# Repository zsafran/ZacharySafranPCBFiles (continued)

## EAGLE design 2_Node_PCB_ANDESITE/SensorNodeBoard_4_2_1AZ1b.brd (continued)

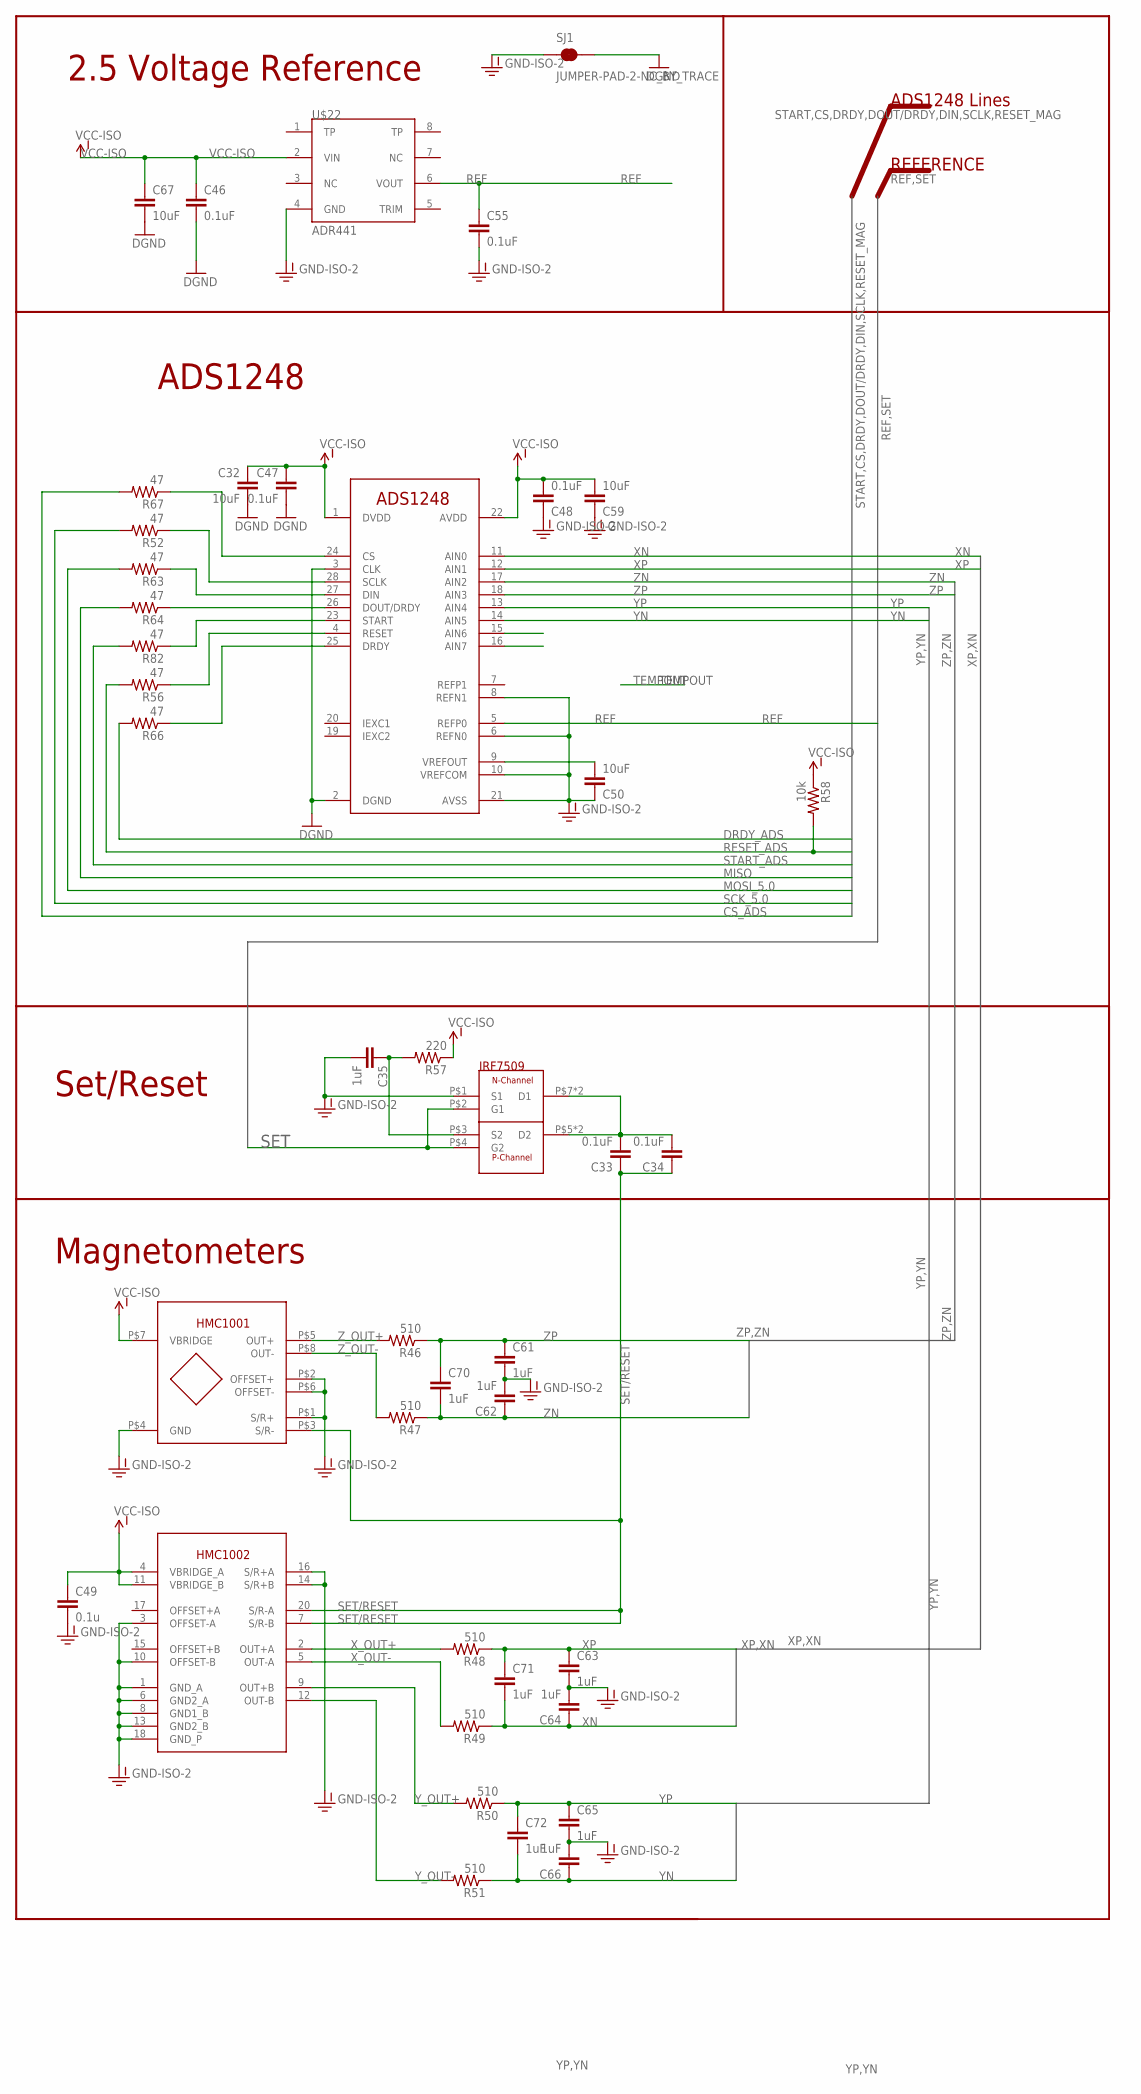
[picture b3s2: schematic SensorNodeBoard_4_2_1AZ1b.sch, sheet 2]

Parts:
C32, C50, C59, C67: 10uF; 0603-CAP
C33, C34, C46, C47, C48, C55: 0.1uF; 0603-CAP
C35, C61, C62, C63, C64, C65, C66, C70, C71, C72: 1uF; 0603-CAP
C49: 0.1u; 0603-CAP
R46, R47, R48, R49, R50, R51: 510; 0603-RES
R52, R56, R63, R64, R66, R67, R82: 47; 0603-RES
R57: 220; 0603-RES
R58: 10k; 0603-RES
SJ1: JUMPER-PAD-2-NC_BY_TRACE; PAD-JUMPER-2-NC_BY_TRACE_YES_SILK
U$7: ADS1248; TSSOP28
U$11: HMC1002; SOIC20R
U$12: HMC1001
U$17: IRF7509; MICRO8
U$22: ADR441; SOIC8

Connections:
ADS4: R56.1, U$7.4 (RESET)
ADS9: C50.2, U$7.9 (VREFOUT)
ADS15: U$7.15 (AIN6)
ADS16: U$7.16 (AIN7)
ADS23: R82.1, U$7.23 (START)
ADS24: R67.1, U$7.24 (CS)
ADS25: R66.1, U$7.25 (DRDY)
ADS26: R64.1, U$7.26 (DOUT/DRDY)
ADS27: R63.1, U$7.27 (DIN)
ADS28: R52.1, U$7.28 (SCLK)
CS_ADS: R67.2; also elsewhere on the board
DRDY_ADS: R66.2; also elsewhere on the board
GND: C32.2, C46.2, C47.2, C67.2, SJ1.2, U$7.2 (DGND), U$7.3 (CLK); also elsewhere on the board
GND-ISO-2: C35.2, C48.1, C49.2, C50.1, C55.2, C59.1, C61.2, C62.2, C63.2, C64.2, C65.2, C66.2, SJ1.1, U$7.6 (REFN0), U$7.8 (REFN1), U$7.10 (VREFCOM), U$7.21 (AVSS), U$11.1 (GND_A), U$11.3 (OFFSET-A), U$11.6 (GND2_A), U$11.8 (GND1_B), U$11.10 (OFFSET-B), U$11.13 (GND2_B), U$11.14 (S/R+B), U$11.16 (S/R+A), U$11.18 (GND_P), U$12.P$1 (S/R+), U$12.P$2 (OFFSET+), U$12.P$4 (GND), U$12.P$6 (OFFSET-), U$17.P$1 (S1), U$22.4 (GND)
MISO: R64.2; also elsewhere on the board
MOSI_5.0: R63.2; also elsewhere on the board
unnamed: C33.2, C34.2, U$17.P$5 (D2), U$17.P$6 (D2), U$17.P$7 (D1), U$17.P$8 (D1)
unnamed: C35.1, R57.2, U$17.P$3 (S2)
REF: C55.1, U$7.5 (REFP0), U$22.6 (VOUT)
RESET_ADS: R56.2, R58.2; also elsewhere on the board
SCK_5.0: R52.2; also elsewhere on the board
SET: U$17.P$2 (G1), U$17.P$4 (G2); also elsewhere on the board
SET/RESET: C33.1, C34.1, U$11.7 (S/R-B), U$11.20 (S/R-A), U$12.P$3 (S/R-)
START_ADS: R82.2; also elsewhere on the board
VCC-ISO: C32.1, C46.1, C47.1, C48.2, C49.1, C59.2, C67.1, R57.1, R58.1, U$7.1 (DVDD), U$7.22 (AVDD), U$11.4 (VBRIDGE_A), U$11.11 (VBRIDGE_B), U$12.P$7 (VBRIDGE), U$22.2 (VIN); also elsewhere on the board
XN: C64.1, C71.2, R49.1, U$7.11 (AIN0)
XP: C63.1, C71.1, R48.1, U$7.12 (AIN1)
X_OUT+: R48.2, U$11.2 (OUT+A)
X_OUT-: R49.2, U$11.5 (OUT-A)
YN: C66.1, C72.2, R51.1, U$7.14 (AIN5)
YP: C65.1, C72.1, R50.1, U$7.13 (AIN4)
Y_OUT+: R50.2, U$11.9 (OUT+B)
Y_OUT-: R51.2, U$11.12 (OUT-B)
ZN: C62.1, C70.2, R47.1, U$7.17 (AIN2)
ZP: C61.1, C70.1, R46.1, U$7.18 (AIN3)
Z_OUT+: R46.2, U$12.P$5 (OUT+)
Z_OUT-: R47.2, U$12.P$8 (OUT-)

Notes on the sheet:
ADS1248 Lines
REFERENCE
ADS1248
Magnetometers
Set/Reset
2.5 Voltage Reference

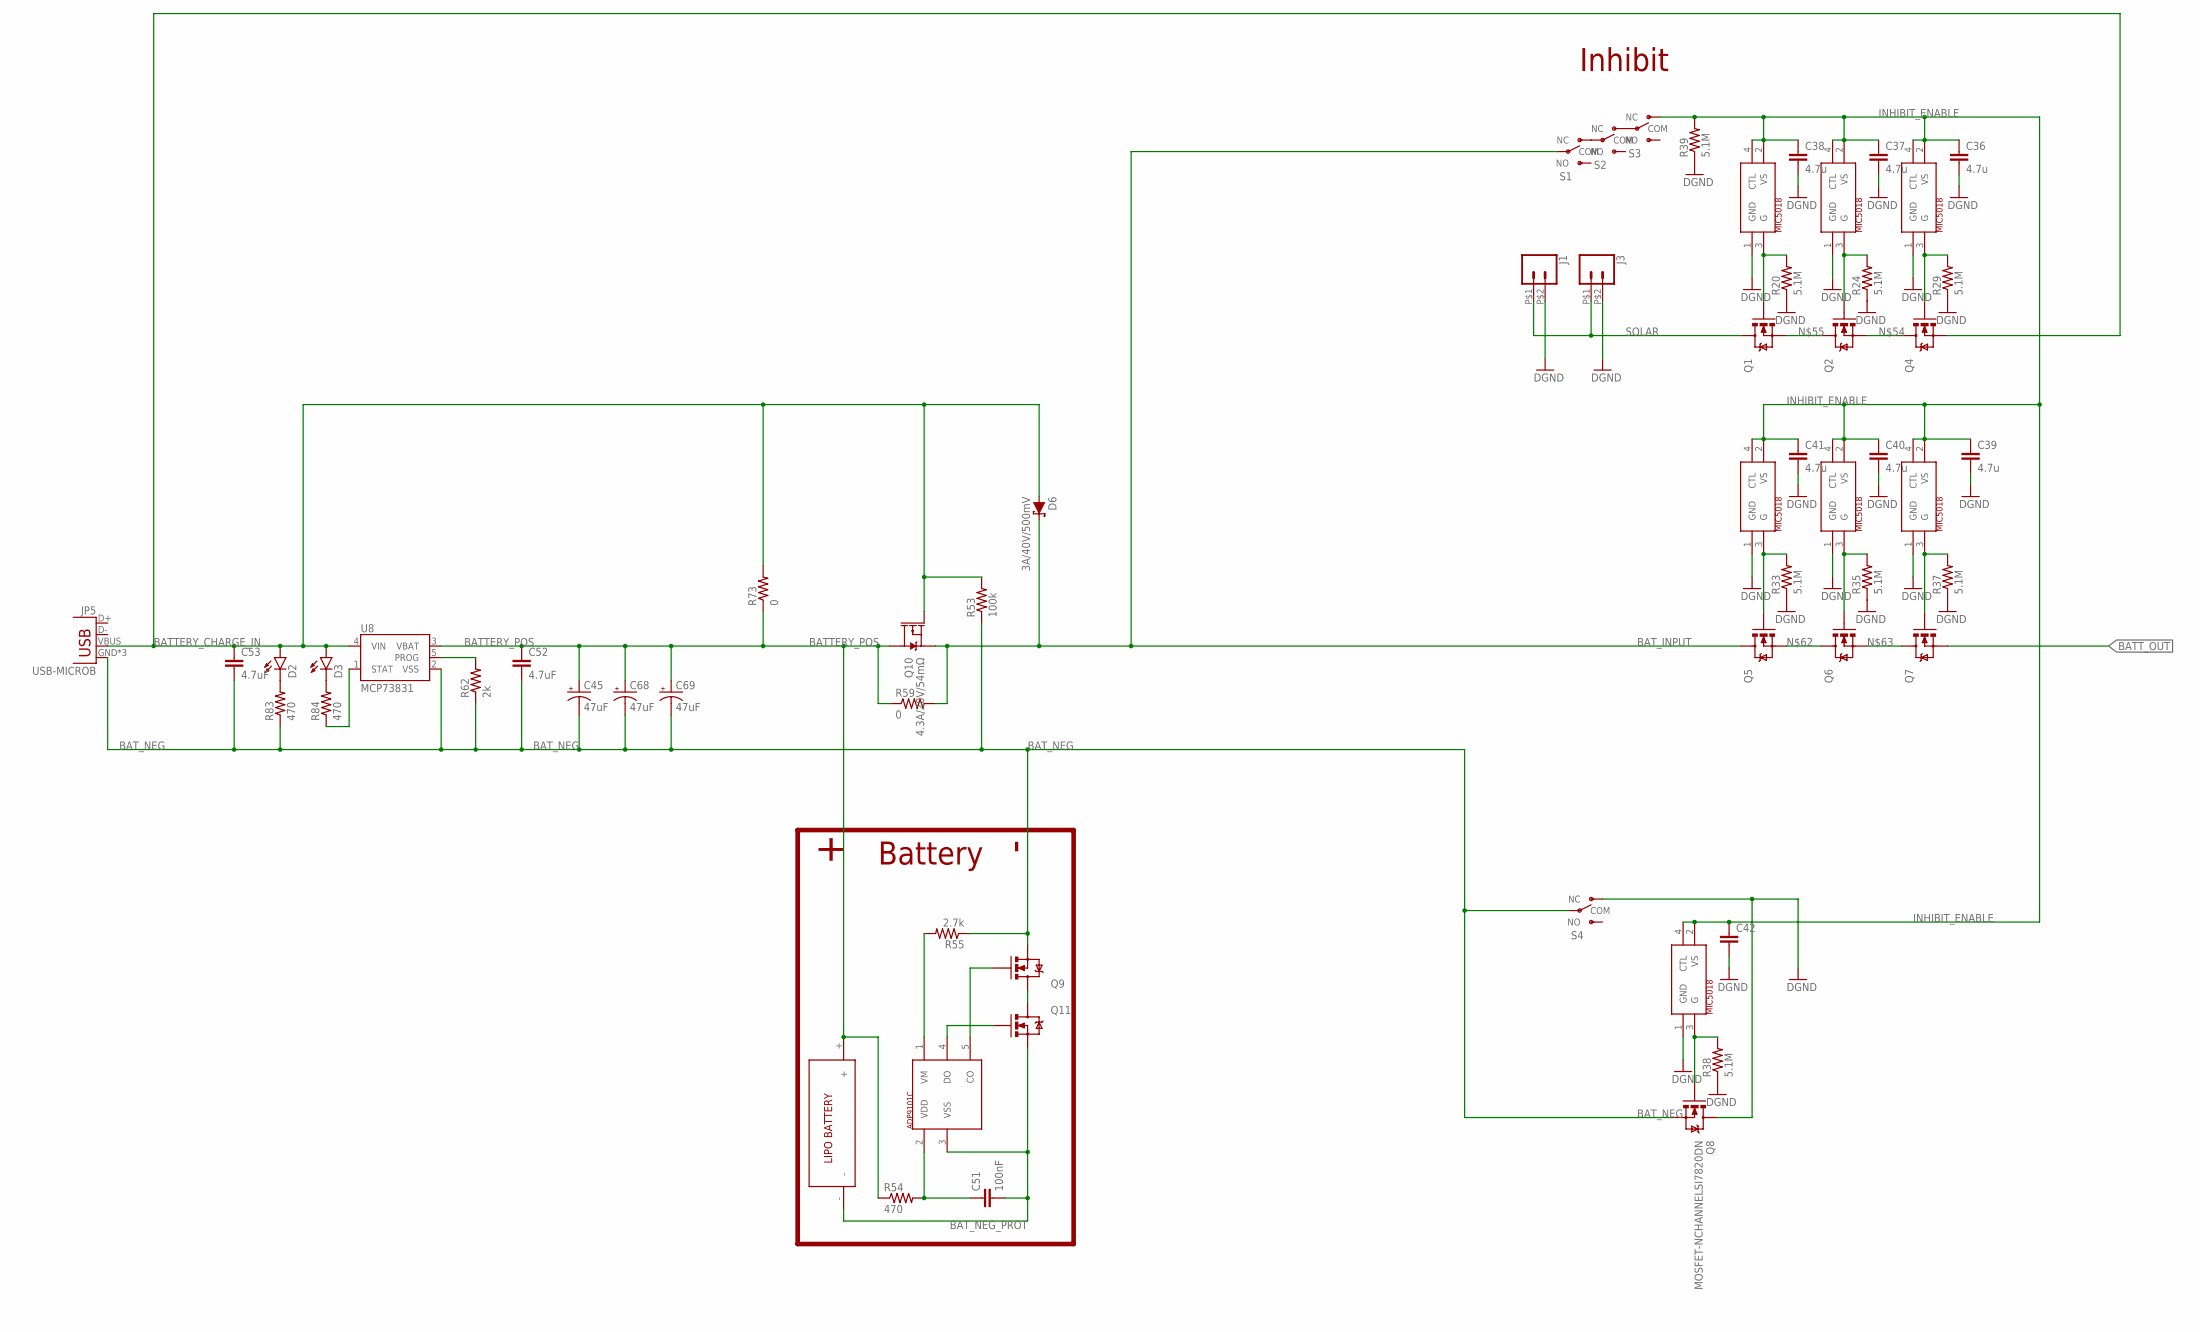
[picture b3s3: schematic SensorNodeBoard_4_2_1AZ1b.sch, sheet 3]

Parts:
C36, C37, C38, C39, C40, C41: 4.7u; 0603-CAP
C42: CAP0603-CAP; 0603-CAP
C45, C68, C69: 47uF; EIA3216
C51: 100nF; 0603-CAP
C52, C53: 4.7uF; 0603-CAP
D2, D3: LED0603; LED-0603
D6: 3A/40V/500mV; SMA-DIODE
J1, J3: CONN_02HIROSE; 1X02_1.25
JP5: USB-MICROB
Q1, Q2, Q4, Q5, Q6, Q7, Q8: MOSFET-NCHANNELSI7820DN; POWERPAK1212-8
Q9, Q11: MOSFET-NCHANNELSSM3K324R; SOT23-3@1
Q10: 4.3A/20V/54mΩ; SOT23-3
R20, R24, R29, R33, R35, R37, R38, R39: 5.1M; 0603-RES
R53: 100k; 0603-RES
R54, R83, R84: 470; 0603-RES
R55: 2.7k; 0603-RES
R59, R73: 0; R2010
R62: 2k; R0603
S1, S2, S3, S4: SWITCH-SPDT; CHERRY_SWITCH
U8: MCP73831; SOT23-5
U$8, U$13, U$14, U$15, U$16, U$19, U$20: MIC5018; SOT143
U$18: BATTERY
U$27: AP9101C; SOT25

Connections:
BATTERY_CHARGE_IN: C53.1, D2.A, D3.A, D6.A, JP5.VBUS, Q4.S1 (S), Q4.S2 (S), Q4.S3 (S), Q10.1 (G), R53.2, R73.2, U8.4 (VIN)
BATTERY_POS: C45.A (+), C52.1, C68.A (+), C69.A (+), Q10.3 (D), R54.1, R59.1, R73.1, U8.3 (VBAT), U$18.+
BATT_OUT: Q7.S1 (S), Q7.S2 (S), Q7.S3 (S); also elsewhere on the board
BAT_INPUT: D6.C, Q5.D1 (D), Q5.D2 (D), Q5.D3 (D), Q5.D4 (D), Q5.DPAD (D), Q10.2 (S), R59.2, S1.COM
BAT_NEG: C45.C (-), C52.2, C53.2, C68.C (-), C69.C (-), JP5.GND, JP5.MT1 (GND), JP5.MT2 (GND), Q8.S1 (S), Q8.S2 (S), Q8.S3 (S), Q9.2 (S), R53.1, R55.1, R62.1, R83.1, S4.COM, U8.2 (VSS)
BAT_NEG_PROT: C51.2, Q11.2 (S), U$18.-, U$27.3 (VSS)
GND: C36.2, C37.2, C38.2, C39.2, C40.2, C41.2, C42.2, J1.P$2 (2), J3.P$2 (2), Q8.D1 (D), Q8.D2 (D), Q8.D3 (D), Q8.D4 (D), Q8.DPAD (D), R20.1, R24.1, R29.1, R33.1, R35.1, R37.1, R38.1, R39.1, S4.NC, U$8.1 (GND), U$13.1 (GND), U$14.1 (GND), U$15.1 (GND), U$16.1 (GND), U$19.1 (GND), U$20.1 (GND); also elsewhere on the board
INHIBIT_ENABLE: C36.1, C37.1, C38.1, C39.1, C40.1, C41.1, C42.1, R39.2, S3.NC, U$8.2 (VS), U$8.4 (CTL), U$13.2 (VS), U$13.4 (CTL), U$14.2 (VS), U$14.4 (CTL), U$15.2 (VS), U$15.4 (CTL), U$16.2 (VS), U$16.4 (CTL), U$19.2 (VS), U$19.4 (CTL), U$20.2 (VS), U$20.4 (CTL)
unnamed: S1.NC, S2.COM
unnamed: S2.NC, S3.COM
unnamed: Q1.G, R20.2, U$8.3 (G)
unnamed: Q2.G, R24.2, U$13.3 (G)
unnamed: Q4.G, R29.2, U$14.3 (G)
unnamed: Q2.S1 (S), Q2.S2 (S), Q2.S3 (S), Q4.D1 (D), Q4.D2 (D), Q4.D3 (D), Q4.D4 (D), Q4.DPAD (D)
unnamed: Q1.S1 (S), Q1.S2 (S), Q1.S3 (S), Q2.D1 (D), Q2.D2 (D), Q2.D3 (D), Q2.D4 (D), Q2.DPAD (D)
unnamed: D2.C, R83.2
unnamed: Q11.1 (G), U$27.4 (DO)
unnamed: Q5.G, R33.2, U$15.3 (G)
unnamed: Q6.G, R35.2, U$16.3 (G)
unnamed: Q7.G, R37.2, U$19.3 (G)
unnamed: Q5.S1 (S), Q5.S2 (S), Q5.S3 (S), Q6.D1 (D), Q6.D2 (D), Q6.D3 (D), Q6.D4 (D), Q6.DPAD (D)
unnamed: Q6.S1 (S), Q6.S2 (S), Q6.S3 (S), Q7.D1 (D), Q7.D2 (D), Q7.D3 (D), Q7.D4 (D), Q7.DPAD (D)
unnamed: Q8.G, R38.2, U$20.3 (G)
unnamed: Q9.1 (G), U$27.5 (CO)
unnamed: Q9.3 (D), Q11.3 (D)
unnamed: R62.2, U8.5 (PROG)
unnamed: R55.2, U$27.1 (VM)
unnamed: C51.1, R54.2, U$27.2 (VDD)
unnamed: D3.C, R84.2
unnamed: R84.1, U8.1 (STAT)
SOLAR: J1.P$1 (1), J3.P$1 (1), Q1.D1 (D), Q1.D2 (D), Q1.D3 (D), Q1.D4 (D), Q1.DPAD (D)

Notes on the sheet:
Battery
Inhibit

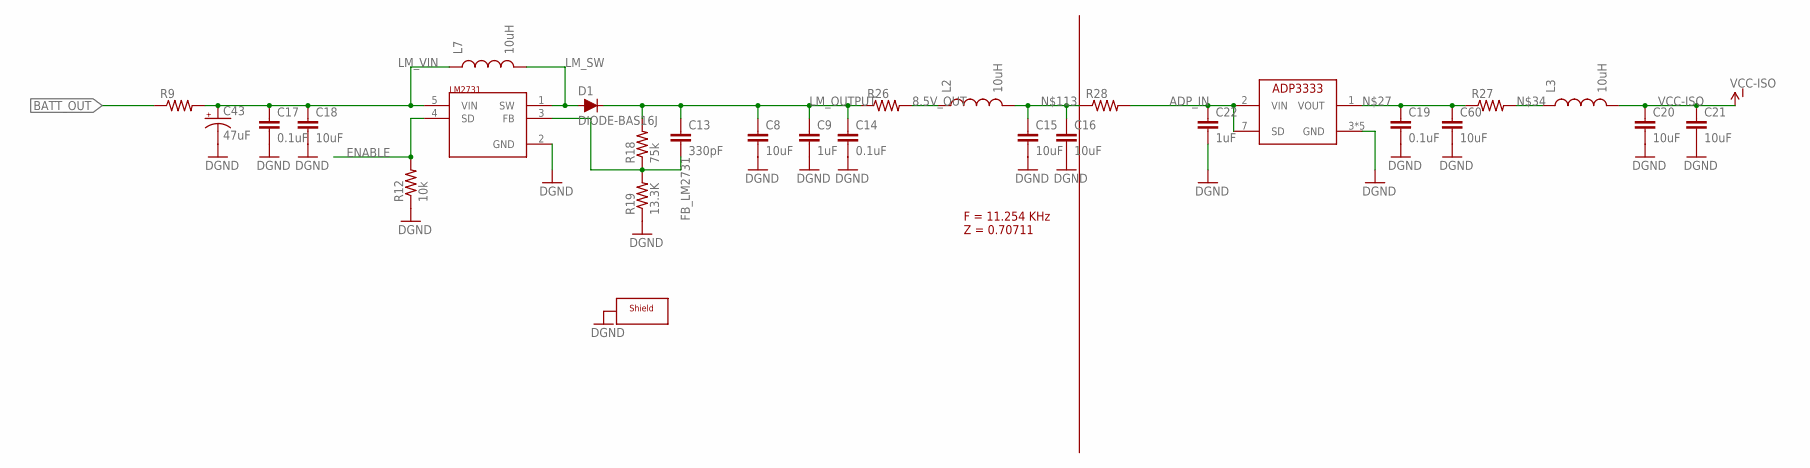
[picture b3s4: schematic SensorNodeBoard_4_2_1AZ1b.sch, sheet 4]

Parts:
C8, C15, C16, C18, C20, C21, C60: 10uF; 0603-CAP
C9, C22: 1uF; 0603-CAP
C13: 330pF; 0603-CAP
C14, C17, C19: 0.1uF; 0603-CAP
C43: 47uF; EIA3216
D1: DIODE-BAS16J; SOD-323
L2, L3, L7: 10uH; 1210
R9, R26, R27, R28: RESISTOR1206; 1206
R12: 10k; 0603-RES
R18: 75k; 0603-RES
R19: 13.3K; 0603-RES
U$4: LM2731; SOT23-5
U$6: ADP3333; MSOP-8
U$37: SHEILD2; SHIELD_BMI-S-209-C

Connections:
8.5V_OUT: L2.1, R26.2
ADP_IN: C22.1, R28.2, U$6.2 (VIN), U$6.7 (SD)
BATT_OUT: R9.1; also elsewhere on the board
ENABLE: R12.2, U$4.4 (SD); also elsewhere on the board
FB_LM2731: C13.2, R18.1, R19.2, U$4.3 (FB)
GND: C8.2, C9.2, C14.2, C15.2, C16.2, C17.2, C18.2, C19.2, C20.2, C21.2, C22.2, C43.C (-), C60.2, R12.1, R19.1, U$4.2 (GND), U$6.3 (GND), U$6.4 (GND), U$6.5 (GND), U$6.6 (GND), U$6.8 (GND), U$37.P$1, U$37.P$2, U$37.P$3, U$37.P$4, U$37.P$5, U$37.P$6, U$37.P$7, U$37.P$8, U$37.P$9, U$37.P$10, U$37.P$11, U$37.P$12, U$37.P$13, U$37.P$14, U$37.P$15, U$37.P$16; also elsewhere on the board
LM_OUTPUT: C8.1, C9.1, C13.1, C14.1, D1.C, R18.2, R26.1
LM_SW: D1.A, L7.2, U$4.1 (SW)
LM_VIN: C17.1, C18.1, C43.A (+), L7.1, R9.2, U$4.5 (VIN)
unnamed: C19.1, C60.1, R27.1, U$6.1 (VOUT)
unnamed 79: L3.1, R27.2; also elsewhere on the board
unnamed: C15.1, C16.1, L2.2, R28.1
VCC-ISO: C20.1, C21.1, L3.2; also elsewhere on the board

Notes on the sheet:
F = 11.254 KHz Z = 0.70711

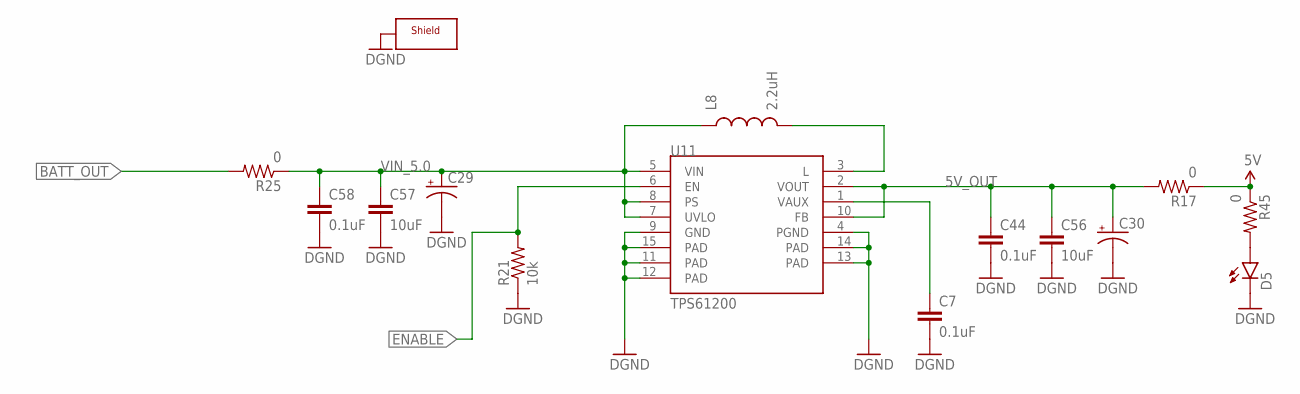
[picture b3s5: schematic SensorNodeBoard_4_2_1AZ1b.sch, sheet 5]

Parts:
C7, C44, C58: 0.1uF; 0603-CAP
C29, C30: CAP_POL1206; EIA3216
C56, C57: 10uF; 0603-CAP
D5: LED0603; LED-0603
L8: 2.2uH; 1210
R17, R25: 0; 1206
R21: 10k; 0603-RES
R45: 0; 0603-RES
U11: TPS61200; QFN-10_PAD
U$39: SHEILD; SHIELD_BMI-S-201-C

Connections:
5V: R17.1, R45.1; also elsewhere on the board
5V_OUT: C30.A (+), C44.1, C56.1, R17.2, U11.2 (VOUT), U11.10 (FB)
BATT_OUT: R25.2; also elsewhere on the board
ENABLE: R21.2, U11.6 (EN); also elsewhere on the board
GND: C7.2, C29.C (-), C30.C (-), C44.2, C56.2, C57.2, C58.2, D5.C, R21.1, U11.4 (PGND), U11.9 (GND), U11.11 (PAD), U11.12 (PAD), U11.13 (PAD), U11.14 (PAD), U11.15 (PAD), U$39.P$1, U$39.P$2, U$39.P$3, U$39.P$4, U$39.P$5, U$39.P$6, U$39.P$7, U$39.P$8, U$39.P$9, U$39.P$10, U$39.P$11, U$39.P$12; also elsewhere on the board
unnamed: L8.2, U11.3 (L)
unnamed: C7.1, U11.1 (VAUX)
unnamed: D5.A, R45.2
VIN_5.0: C29.A (+), C57.1, C58.1, L8.1, R25.1, U11.5 (VIN), U11.7 (UVLO), U11.8 (PS)

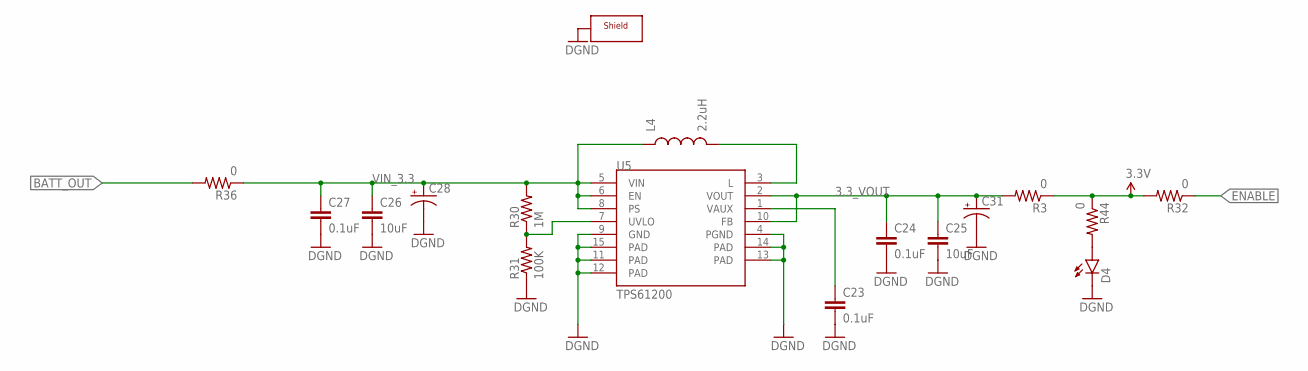
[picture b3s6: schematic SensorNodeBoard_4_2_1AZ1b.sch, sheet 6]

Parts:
C23, C24, C27: 0.1uF; 0603-CAP
C25, C26: 10uF; 0603-CAP
C28, C31: CAP_POL1206; EIA3216
D4: LED0603; LED-0603
L4: 2.2uH; 1210
R3, R36: 0; 1206
R30: 1M; 0603-RES
R31: 100K; 0603-RES
R32, R44: 0; 0603-RES
U5: TPS61200; QFN-10_PAD
U$41: SHEILD; SHIELD_BMI-S-201-C

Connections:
3.3V: R3.1, R32.2, R44.1; also elsewhere on the board
3.3_UVLO: R30.1, R31.2, U5.7 (UVLO)
3.3_VOUT: C24.1, C25.1, C31.A (+), R3.2, U5.2 (VOUT), U5.10 (FB)
BATT_OUT: R36.2; also elsewhere on the board
ENABLE: R32.1; also elsewhere on the board
GND: C23.2, C24.2, C25.2, C26.2, C27.2, C28.C (-), C31.C (-), D4.C, R31.1, U5.4 (PGND), U5.9 (GND), U5.11 (PAD), U5.12 (PAD), U5.13 (PAD), U5.14 (PAD), U5.15 (PAD), U$41.P$1, U$41.P$2, U$41.P$3, U$41.P$4, U$41.P$5, U$41.P$6, U$41.P$7, U$41.P$8, U$41.P$9, U$41.P$10, U$41.P$11, U$41.P$12; also elsewhere on the board
unnamed: L4.2, U5.3 (L)
unnamed: C23.1, U5.1 (VAUX)
unnamed: D4.A, R44.2
VIN_3.3: C26.1, C27.1, C28.A (+), L4.1, R30.2, R36.1, U5.5 (VIN), U5.6 (EN), U5.8 (PS)

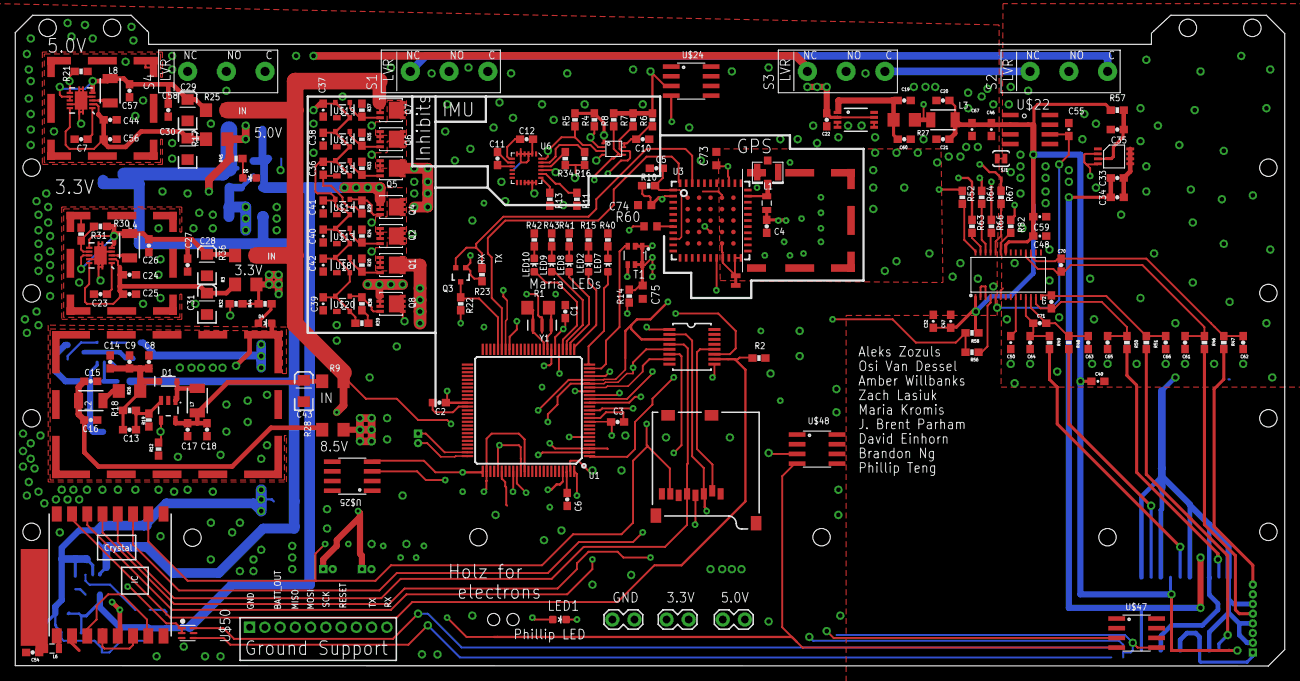
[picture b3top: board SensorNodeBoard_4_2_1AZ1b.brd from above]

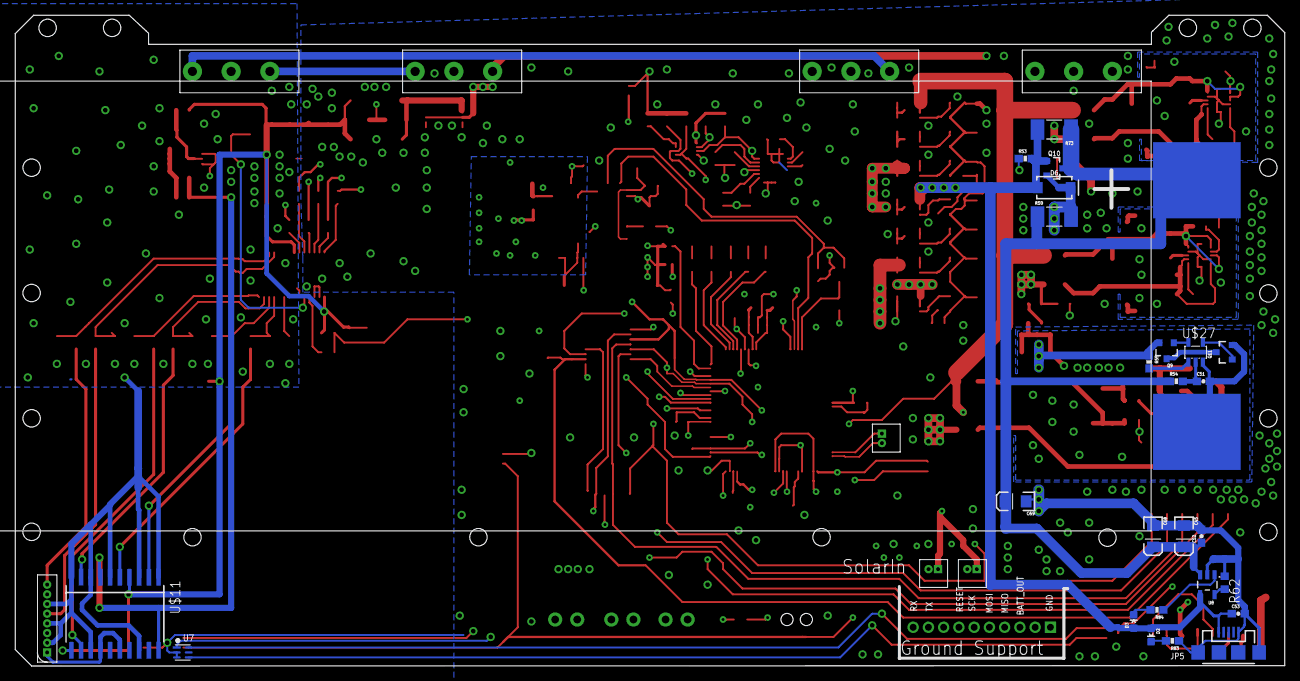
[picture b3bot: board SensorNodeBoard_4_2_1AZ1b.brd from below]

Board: 4 copper layers, 166.5 x 85.3 mm, 228 parts (30 on the bottom side), 143 nets.

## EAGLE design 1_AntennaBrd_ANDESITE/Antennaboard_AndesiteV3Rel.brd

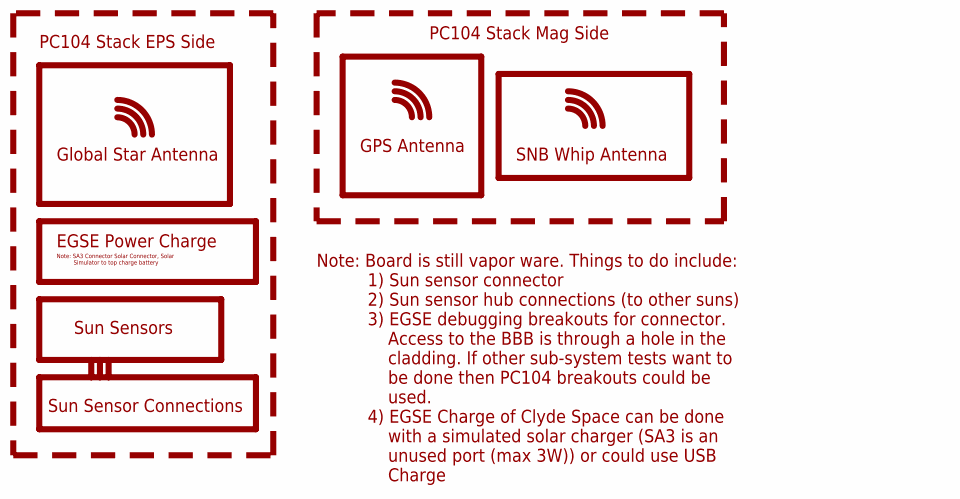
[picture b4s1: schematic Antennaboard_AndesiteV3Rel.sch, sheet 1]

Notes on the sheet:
GPS Antenna
Global Star Antenna
SNB Whip Antenna
PC104 Stack EPS Side
PC104 Stack Mag Side
Sun Sensors
EGSE Power Charge
Note: SA3 Connector Solar Connector, Solar Simulator to top charge battery
Sun Sensor Connections
Note: Board is still vapor ware. Things to do include: 1) Sun sensor connector 2) Sun sensor hub connections (to other suns) 3) EGSE debugging breakouts for connector. Access to the BBB is through a hole in the cladding. If other sub-system tests want to be done then PC104 breakouts could be used. 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

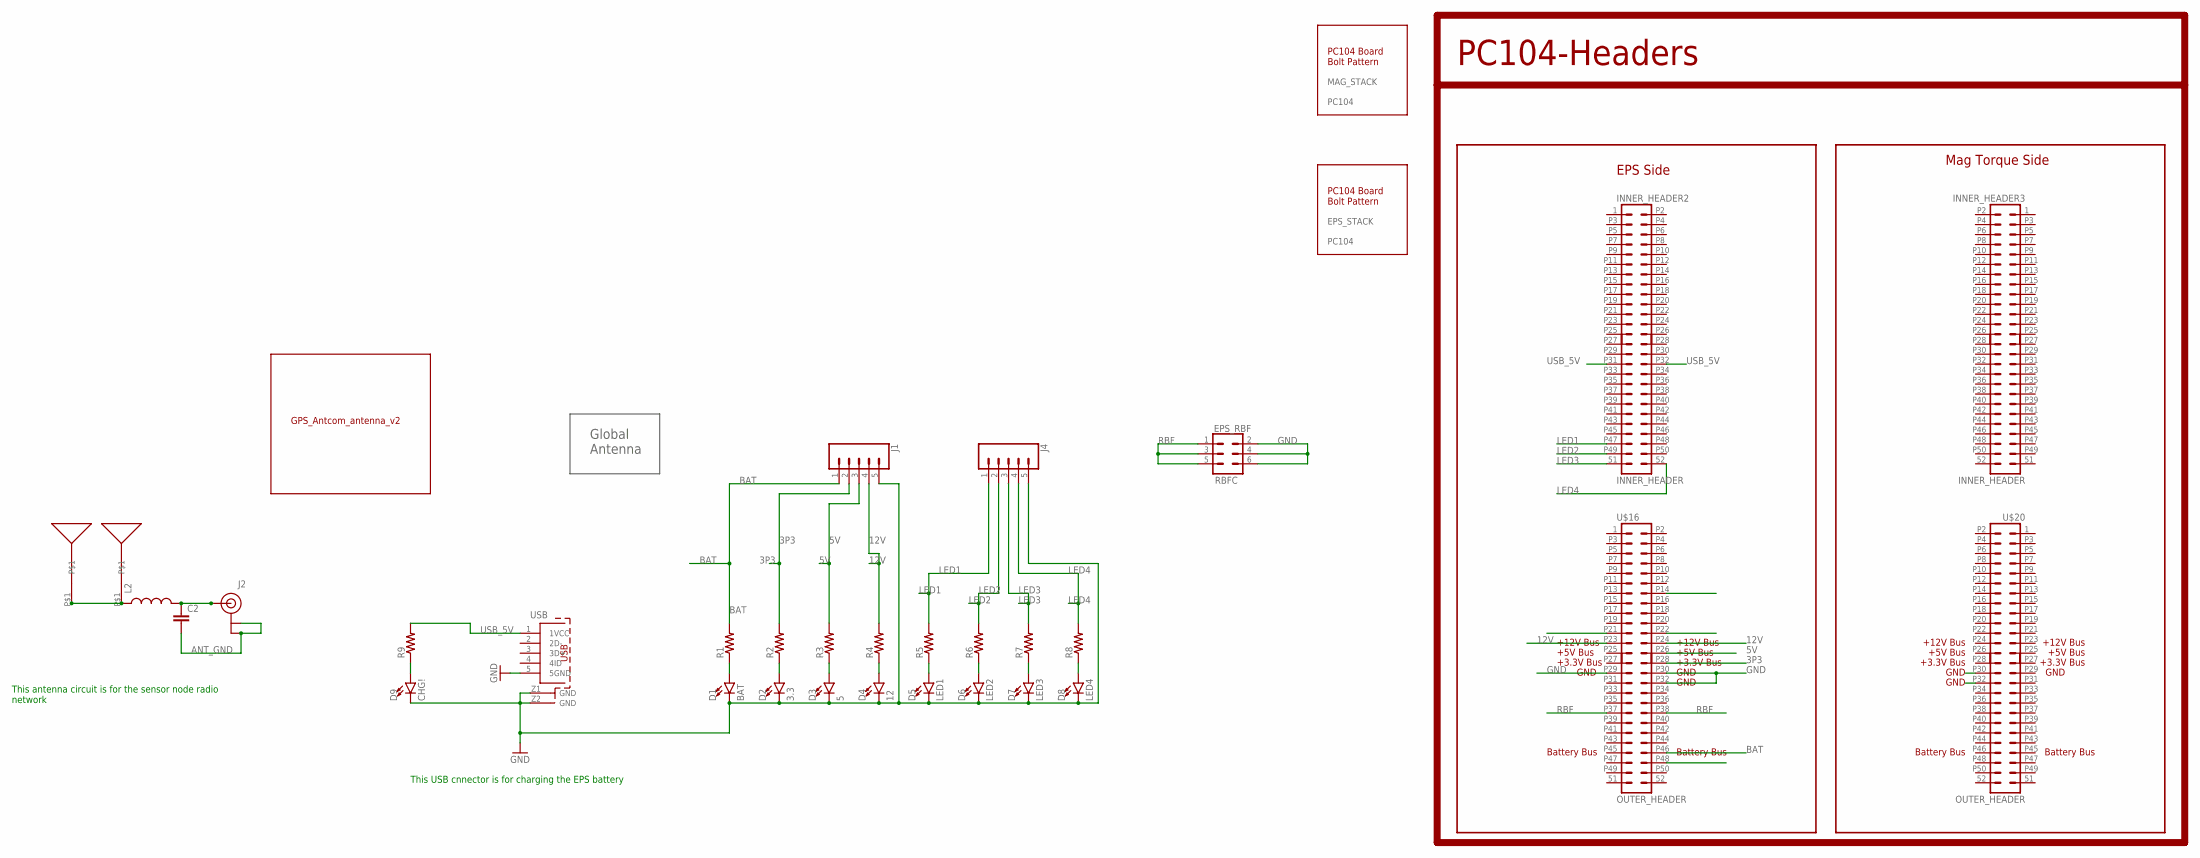
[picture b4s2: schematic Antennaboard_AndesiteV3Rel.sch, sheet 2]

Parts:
C2: CAP1210; 1210
D1: BAT; LED-0603
D2: 3.3; LED-0603
D3: 5; LED-0603
D4: 12; LED-0603
D5: LED1; LED-0603
D6: LED2; LED-0603
D7: LED3; LED-0603
D8: LED4; LED-0603
D9: CHG!; LED-0603
EPS_RBF: RBFC; 2X3
EPS_STACK: PC104
INNER_HEADER2, INNER_HEADER3: INNER_HEADER; 2X26
J1, J4: CONN_05NO_SILK; 1X05_NO_SILK
J2: U.FL
L2: INDUCTOR1210; 1210
MAG_STACK: PC104
R1, R2, R3, R4, R5, R6, R7, R8, R9: R-US_R0603; R0603
U$1: ANTENNA; GLOBAL_ANTENNA
U$2: GPS_ANTCOM_ANTENNA; GPS_ANTCOM_2
U$3, U$18: SNB_ANT; SLOT
U$16, U$20: OUTER_HEADER; 2X26
USB: 614105150721

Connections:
3P3: J1.2, R2.2, U$16.P28
5V: J1.3, R3.2, U$16.P26 (26)
12V: J1.4, R4.2, U$16.P23 (23), U$16.P24 (24)
ANT_GND: C2.2, J2.P$1 (GND), J2.P$2 (GND)
BAT: J1.1, R1.2, U$16.P46 (46)
GND: D1.C, D2.C, D3.C, D4.C, D5.C, D6.C, D7.C, D8.C, D9.C, EPS_RBF.2, EPS_RBF.4, EPS_RBF.6, J1.5, J4.5, U$16.P21 (21), U$16.P22 (22), U$16.P29, U$16.P30, U$16.P32, U$16.P48 (48), USB.5 (5GND), USB.Z1 (GND), USB.Z2 (GND)
LED1: INNER_HEADER2.P47 (47), J4.1, R5.2
LED2: INNER_HEADER2.P49 (49), J4.2, R6.2
LED3: INNER_HEADER2.51, J4.3, R7.2
LED4: INNER_HEADER2.52, J4.4, R8.2
unnamed: D9.A, R9.1
unnamed: D1.A, R1.1
unnamed: D2.A, R2.1
unnamed: D3.A, R3.1
unnamed: D4.A, R4.1
unnamed: D5.A, R5.1
unnamed: D6.A, R6.1
unnamed: D7.A, R7.1
unnamed: D8.A, R8.1
unnamed: C2.1, J2.P$3 (SIGNAL), L2.2
unnamed: L2.1, U$3.P$1, U$18.P$1
RBF: EPS_RBF.1, EPS_RBF.3, EPS_RBF.5, U$16.P37 (37), U$16.P38 (38)
USB_5V: INNER_HEADER2.P31, INNER_HEADER2.P32, R9.2, USB.1 (1VCC)

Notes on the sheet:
PC104-Headers
EPS Side
Mag Torque Side
This antenna circuit is for the sensor node radio network
This USB cnnector is for charging the EPS battery

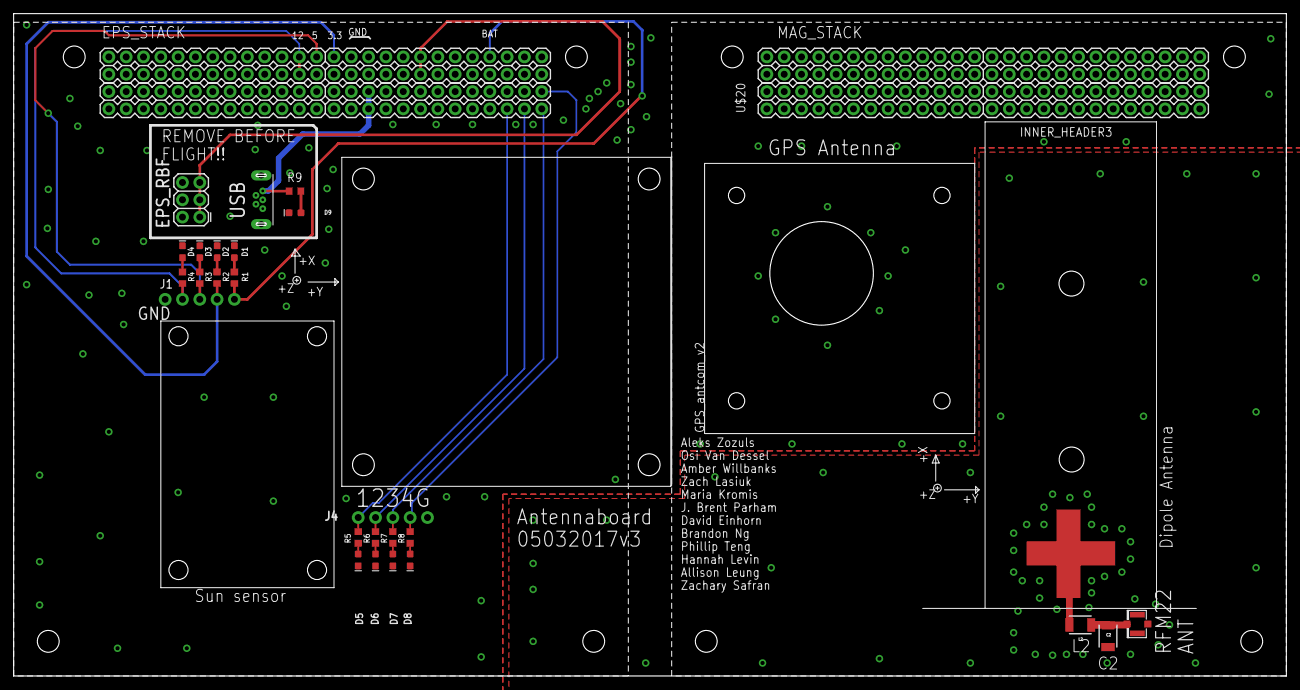
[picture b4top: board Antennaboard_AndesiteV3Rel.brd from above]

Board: 2 copper layers, 186.7 x 97.2 mm, 35 parts (0 on the bottom side), 23 nets.

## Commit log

2018-10-21 Added Eagle PCB files
    Added Eagle PCB files
2018-10-21 Altium Accelerometer PCB added
    Altium Accelerometer PCB added
2018-10-21 Uploaded images
    Uploaded images
2018-10-21 Updated README #1
2018-10-21 Updated README and added more photos
2018-10-21 Renamed picture
2018-10-21 Revert "Renamed picture"
    This reverts commit 21f2a703a37ad5f063decfb02db99ca1d36902a8.
2018-10-21 Updated README and added pictures #2
2018-10-22 Added Altium files
2018-10-22 Updateed READMED.md
